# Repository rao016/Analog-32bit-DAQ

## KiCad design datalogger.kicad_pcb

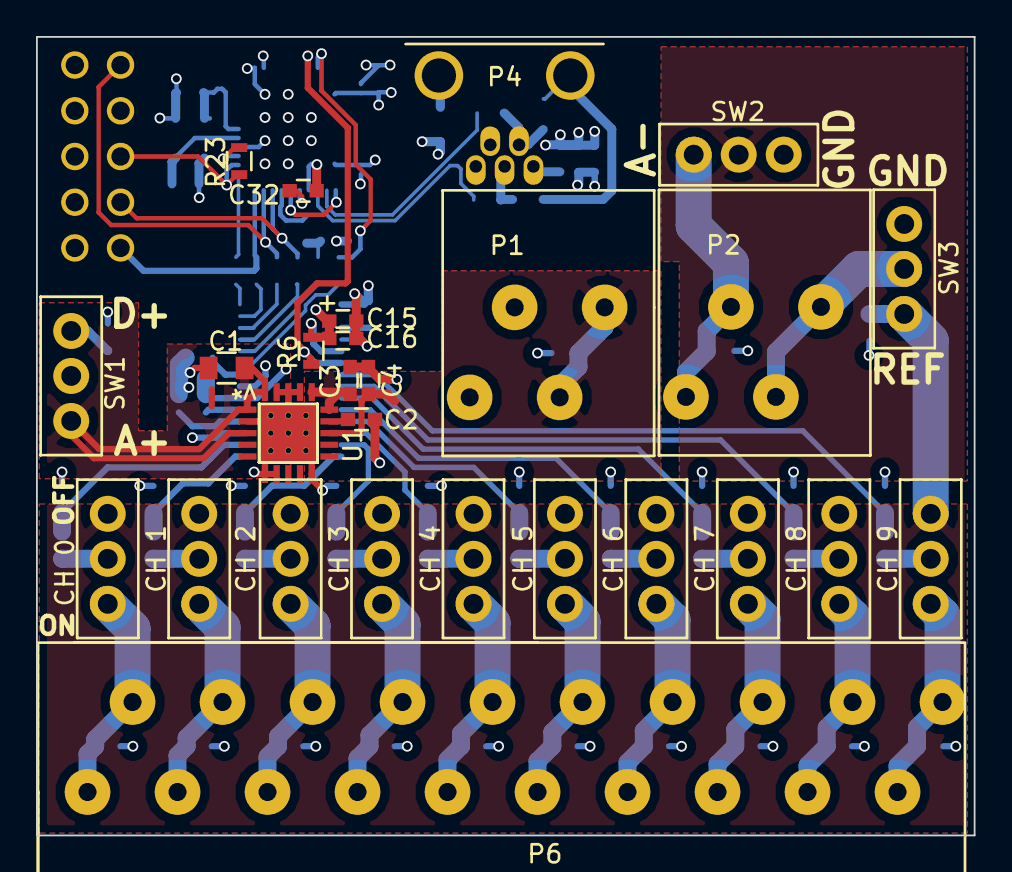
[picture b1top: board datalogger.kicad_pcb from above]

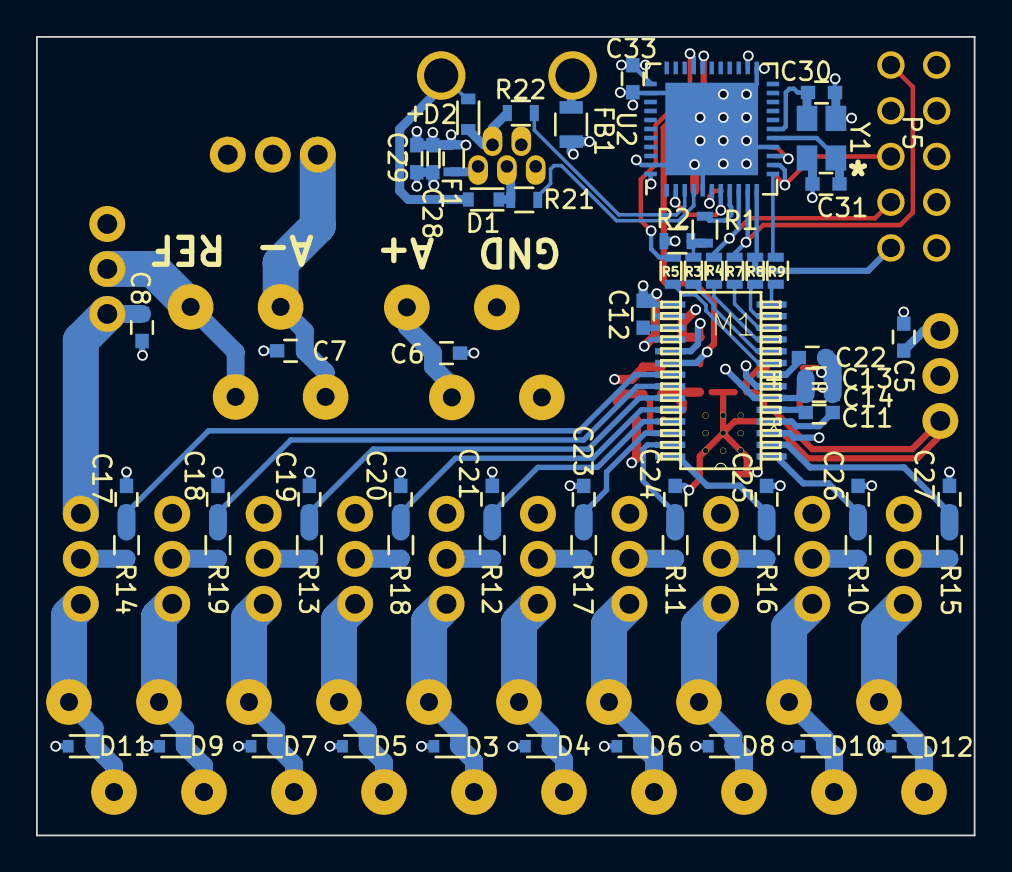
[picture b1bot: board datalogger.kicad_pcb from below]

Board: 4 copper layers, 52.1 x 44.4 mm, 89 parts (62 on the bottom side), 67 nets.

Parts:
C1: 47uF; C_0805
C2, C3, C4, C12, C22, C32: 1uF; C_0603
C5, C6, C7, C8, C33: 10uF; C_0603
C11: 4.7nF; C_0603
C13, C16: 1uF; C_0603T
C14, C15, C28: 0.1uF; C_0603
C17, C18, C19, C20, C21, C23, C24, C25, C26, C27: C; C_0603
C29: 10uF; C_0603T
C30, C31: 18pF; C_0603
CH 0, CH 1, CH 2, CH 3, CH 4, CH 5, CH 6, CH 7, CH 8, CH 9: SWITCH_INV; switch
D1, D2: PGB1010; D_0603
D3, D4, D5, D6, D7, D8, D9, D10, D11, D12: PESD5V0U1UL; SOD-523
F1: F_Small; R_0603
FB1: BLM21; R_0805
M1: ADS1263_PW_28; PW28
P1: A+ Battery; 2pinConn
P2: A- Battery; 2pinConn
P4: USB_B; usbB
P5: CONN_02X05; con5x2
P6: CONN_01X10; 10pinConn
R1, R2: 0; R_0603
R3, R4, R5, R7, R8, R9: 47; R_0603
R6, R23: 10K; R_0603
R10, R11, R12, R13, R14, R15, R16, R17, R18, R19: R; R_0603
R21, R22: 22; R_0603
SW1, SW2, SW3: SWITCH_INV; switch
U1: TPS7A4700RGWT; TPS7A470x
U2: ATMEGA32U4-M; QFN-44-1EP_7x7mm_Pitch0.5mm
Y1: Crystal; crystal

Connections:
/ADC/AIN0: CH 9.2, R14.1
/ADC/AIN1: CH 8.2, R19.1
/ADC/AIN2: CH 7.2, R13.1
/ADC/AIN3: CH 6.2, R18.1
/ADC/AIN4: CH 5.2, R12.1
/ADC/AIN5: CH 4.2, R17.1
/ADC/AIN6: CH 3.2, R11.1
/ADC/AIN7: CH 2.2, R16.1
/ADC/AIN8: CH 1.2, R10.1
/ADC/AIN9: CH 0.2, R15.1
/ADC/CS: R1.2, U2.8
/ADC/DRDY: R9.1, U2.12
/ADC/PWDN: M1.20, R6.1, U2.29
/ADC/RX: P5.1, R7.2, U2.10
/ADC/SCK: P5.7, R4.2, U2.9
/ADC/START: R5.2, U2.30
/Interface/SPI_RXD: P5.9, R8.1, U2.11
A5V: C13.1, C14.1, M1.6, SW1.2
A+: C3.1, C4.1, C6.2, P1.1, U1.13, U1.15, U1.16
AGND: C1.2, C2.2, C3.2, C4.2, C5.1, C6.1, C7.2, C8.1, C12.1, C13.2, C14.2, C15.2, C16.2, C17.2, C18.2, C19.2, C20.2, C21.2, C22.1, C23.2, C24.2, C25.2, C26.2, C27.2, C28.1, C29.2, C30.1, C31.2, C32.2, C33.1, D3.2, D4.2, D5.2, D6.2, D7.2, D8.2, D9.2, D10.2, D11.2, D12.2, FB1.1, M1.7, M1.15, M1.18, P1.2, P4.4, P5.4, P5.6, P5.8, P5.10, R2.1, SW2.3, SW3.1, U1.2, U1.6, U1.7, U1.10, U1.17, U1.18, U1.19, U2.5, U2.15, U2.23, U2.35, U2.43, U2.45, Y1.3, Y1.4
AREF: C8.2, CH 0.1, CH 1.1, CH 2.1, CH 3.1, CH 4.1, CH 5.1, CH 6.1, CH 7.1, CH 8.1, CH 9.1, M1.3, SW3.3
D5V: C5.2, C15.1, C16.1, C28.2, C29.1, C33.2, F1.2, M1.19, P5.2, R6.2, R23.1, SW1.3, U2.2, U2.7, U2.14, U2.24, U2.34, U2.44
unnamed: C1.1, SW1.1, U1.1, U1.3, U1.20
unnamed: C2.1, U1.14
unnamed: C7.1, P2.2, SW2.1
unnamed: C11.1, M1.5
unnamed: C11.2, M1.4
unnamed: C12.2, M1.17
unnamed: C17.1, M1.21, R14.2
unnamed: C18.1, M1.22, R19.2
unnamed: C19.1, M1.23, R13.2
unnamed: C20.1, M1.24, R18.2
unnamed: C21.1, M1.25, R12.2
unnamed: C22.2, M1.8
unnamed: C23.1, M1.26, R17.2
unnamed: C24.1, M1.27, R11.2
unnamed: C25.1, M1.28, R16.2
unnamed: C26.1, M1.1, R10.2
unnamed: C27.1, M1.2, R15.2
unnamed: C30.2, U2.17, Y1.2
unnamed: C31.1, U2.16, Y1.1
unnamed: C32.1, U2.6
unnamed: D1.1, P4.3, R21.2
unnamed: D1.2, D2.2, FB1.2, P4.5
unnamed: D2.1, P4.2, R22.2
unnamed: CH 5.3, D3.1, P6.6
unnamed: CH 4.3, D4.1, P6.5
unnamed: CH 6.3, D5.1, P6.7
unnamed: CH 3.3, D6.1, P6.4
unnamed: CH 7.3, D7.1, P6.8
unnamed: CH 2.3, D8.1, P6.3
unnamed: CH 8.3, D9.1, P6.9
unnamed: CH 1.3, D10.1, P6.2
unnamed: CH 9.3, D11.1, P6.10
unnamed: CH 0.3, D12.1, P6.1
unnamed: F1.1, P4.1
unnamed: M1.9, R5.1
unnamed: M1.10, R3.1
unnamed: M1.11, R4.1
unnamed: M1.12, R7.1
unnamed: M1.13, R8.2
unnamed: M1.14, R9.2
unnamed: P2.1, SW3.2
unnamed: P5.5, R23.2, U2.13
unnamed: R1.1, R2.2, R3.2
unnamed: R21.1, U2.4
unnamed: R22.1, U2.3

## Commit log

2017-04-03 Rev 1
    Working condition, but processor is a little slow for data throughput
